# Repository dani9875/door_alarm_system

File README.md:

# Door alarm system
This project is a DIY smart door alarm system designed to enhance property security by providing real-time monitoring and notifications. The system detects whether a door has been opened or closed and instantly reacts to these events.

When a change is detected, the system transmits the event data through the local network to cloud services. The cloud then relays the information to a mobile application, alerting the property owner via a notification. This ensures the owner is promptly informed whenever someone enters or leaves the property.

*In case you are interested in making your own instance, please find the HW manufacturing files under the release tab.*

# How to build, flash and monitor the output the firmware
0. Check out the repository

1. Navigate to the `door_alarm_fw` directory:  
   ```bash
   cd door_alarm_fw
   ```

2. (Once) Build the Docker image by executing the following script if you have not done yet:  
   ```bash
   ./docker_build.sh
   ```

3. After the Docker image is successfully built, start the container using:  
   ```bash
   ./docker_start.sh
   ```

4. Configure the followings in *main.c* manually before build:

   ```c
   #define EXAMPLE_ESP_WIFI_SSID      "AP"
   #define EXAMPLE_ESP_WIFI_PASS      "password"

   #define EXAMPLE_STATIC_IP_ADDR        "192.168.0.100"
   #define EXAMPLE_STATIC_GW_ADDR        "192.168.0.1"
   #define EXAMPLE_STATIC_NETMASK_ADDR   "255.255.255.0"

   #define HOST "us-east-1-1.aws.cloud2.influxdata.com"
   #define PATH "/api/v2/write?orgID=[org_id]&bucket=[bucket_name]&precision=ns"
   #define TOKEN "Token [INFLUX_DB TOKEN]"
   ```

5. Inside the container, build the firmware by running:  
   ```bash
   ./build_firmware.sh
   ```

6. To program the firmware onto the device, use:  
   ```bash
   ./burn_firmware.sh
   ```

7. If you wish to observe the firmware's output, execute the monitoring script:  
   ```bash
   ./monitor_firmware.sh
   ```

## Release notes

### Version: v3.0
Changelog:
- Voltage divider resistor change
- Component library update

### Version: v2.0
Changelog:
- Component library organised
- Fuse introduced
- IP4283CZ10-TBR,115 ESD diodes

### Version: v1.0
Changelog:
- USB capability (does not work)
- USB active LED (erroneously glows even when operating from battery)
- Debug programming header
- Reed switch gate 
- Debug LED
- Voltage sense

# Technical solutions
The heart of the device is the reed sensor, which operates in normally open mode (the circuit remains open when the magnet and the reed sensor are aligned). This design choice minimizes power consumption, as no current is drawn when the door is closed. The system remains in deep sleep mode most of the time and can only be interrupted by an interaction, such as opening or closing the door. When the system wakes up, it checks the battery charge level and the door status, then initializes the WiFi connection to transmit this data to the cloud. 

A time-series data platform, [Influx](https://cloud2.influxdata.com/signup), is used to collect the data, and the data is forwarded to [Grafana](https://grafana.com/) for visualization. You can find the `grafana_door_alarm_system.json` file in the docs, which you can import to create a dashboard for monitoring the door status and battery level. Make sure to set the source ID (UID) to ensure proper functionality. 

If you would like to receive notifications about state changes, I recommend visiting [IFTTT](https://ifttt.com/explore). You can trigger events and subscribe to them. The ideal solution is to create a webhook that can be triggered from the ESP32 when it wakes up. However, this is a PRO feature. If you want to stay within the free tier, you can create a Google Sheet, set it as a trigger, and add a row (GDrive API is enabled). When a row is added, the subscriber can receive a WhatsApp message (note that with the free plan, the message may be delayed up to 1 hour).

### V2
After the component placement, I realized that the voltage measurement enable pin pad came off, so I rewired it to the LED enable pin. As a result, every time I measure the battery level, the LED briefly lights up. I also didn't have a fuse in my inventory, so I bypassed it with a direct connection. Since USB communication was functioning properly, I decided not to add the H1 straight header pins.

**How to check if the USB interface is working properly:**

Run ```lsusb``` and look for a device called ```Espressif USB JTAG/serial debug unit``` 

```bash
root@c7cc3ff0b21c:/project# lsusb
Bus 004 Device 001: ID 1d6b:0003  
Bus 003 Device 003: ID 046d:c52b Logitech USB Receiver
Bus 003 Device 002: ID 13d3:54b1 Azurewave Integrated Camera
Bus 003 Device 021: ID 303a:1001 Espressif USB JTAG/serial debug unit
Bus 003 Device 004: ID 0bda:c123 Realtek Bluetooth Radio
Bus 003 Device 001: ID 1d6b:0002  
Bus 002 Device 001: ID 1d6b:0003  
Bus 001 Device 001: ID 1d6b:0002 
```

**A short code snippet (main.c, app_main()) that allows you to check if the general LED blinks:**
```c
const uint8_t led_en = GPIO_NUM_14;

void app_main(void)
{
    gpio_reset_pin(led_en);
    gpio_set_direction(led_en, GPIO_MODE_OUTPUT);

    while(1)
    {
        gpio_set_level(led_en, 1);
        vTaskDelay(pdMS_TO_TICKS(1000));
        gpio_set_level(led_en, 0);
        vTaskDelay(pdMS_TO_TICKS(1000));
    }   

    return;
}
```
In a short test, I approached the reed sensor with the magnet, which triggered a wake-up event (the LED lights up). While I held the magnet in place, nothing further happened, and the device went back to sleep. As soon as I removed the magnet, the LED flashed again, indicating that the system had woken up, similar to how it would behave if the door were opened. </br>

Although I did not have a proper casing the setup was mounted above the entrance to collect data and analyze power consumption. Data was being monitored in Grafana. 

</br>

### V1
The first version was revised because the USB interface did not work at all, and it wasn’t even impedance-controlled. As a result, it had to be programmed via the UART interface using a USB-to-TTL adapter.

## Consumption calculations
Power usage estimates assume the application wakes up 6 times a day (3 times for door opening and 3 times for door closing), and the system is powered by 4 AA batteries with average capacity.

| **Component**              | **Current (µA)** | **Time (s)** | **Energy Contribution (µA·s)**   | **Comment**                                                                                          |
|----------------------------|------------------|--------------|-----------------------------------|------------------------------------------------------------------------------------------------------|
| AP2114HA-3.3TRG1           | 60              | 86400        | 60*86400 = 5184000  | LDO operates at all times.                                                                          |
| ESP32 awake doing its job  | 300000          | 60           | 300000*60 = 18000000| Wake-up duration is approximately 10 seconds.                                                      |
| Battery measurement        | 240             | 60           | 240*60 = 14400   | V_SENSE divider: ~ (6 V / 25000 Ω) = 240 µA, active only during wake-up periods.                    |
| Reed switch closed (door open)    | 330             | 45           | 330*45 = 14850      | The door is left open for a maximum of 15 seconds, and this state occurs during half of all activities. |
| ESP32 deep sleep mode      | 8               | 86340        | 8*86340 = 690720    | ESP32 consumes minimal power during deep sleep.                                                     |

#### Total Energy Contribution (µA·s):
$$
5184000 + 18000000 + 14400 + 14850 + 690720 = 23903970 \ \text{µAs}
$$

#### Average Current per day (µA):
$$
\text{Average Current} = \frac{23903970}{86400} \approx 276 \ \text{µA}
$$

**Assumptions:**
**4 AA batteries** in series: Each AA battery provides **1.5V**, and the combined voltage will be **6V**. **Capacity of AA batteries**: We'll assume **2000 mAh** for typical alkaline AA batteries. **Average current consumption**: **276 µA** (0.276 mA).
</br>

#### Battery life in hours can be calculated by dividing the total battery capacity by the current draw:

$$
\text{Battery Life (hours)} = \frac{\text{Battery Capacity (mAh)}}{\text{Current Consumption (mA)}}
$$

#### For **2000 mAh** batteries and **0.276 mA** current:

$$
\text{Battery Life (hours)} = \frac{2000}{0.276} \approx 7246 \, \text{hours}
$$

#### Convert this to days:

$$
\text{Battery Life (days)} = \frac{7246}{24} \approx 302 \, \text{days}
$$

**Calculation here is not final since batteries are not drained to 0 V. Will be added after some testing. LDO shall be fed at least from 4V.** 

## Limitations/what could be improved
- HW routing is not ideal
- Local wifi credentials and static IP as well as INFLUX_DB credentials must be compiled into the project and must be set from source code
- Consumptions increase when the door is open (around 400-500 uA)
- HW and FW project is tightly-coupled making versioning obscure
- Voltage divider resistors are mixed up
- Creation of a elegant enclosure is lacked
- Some FW clean-up

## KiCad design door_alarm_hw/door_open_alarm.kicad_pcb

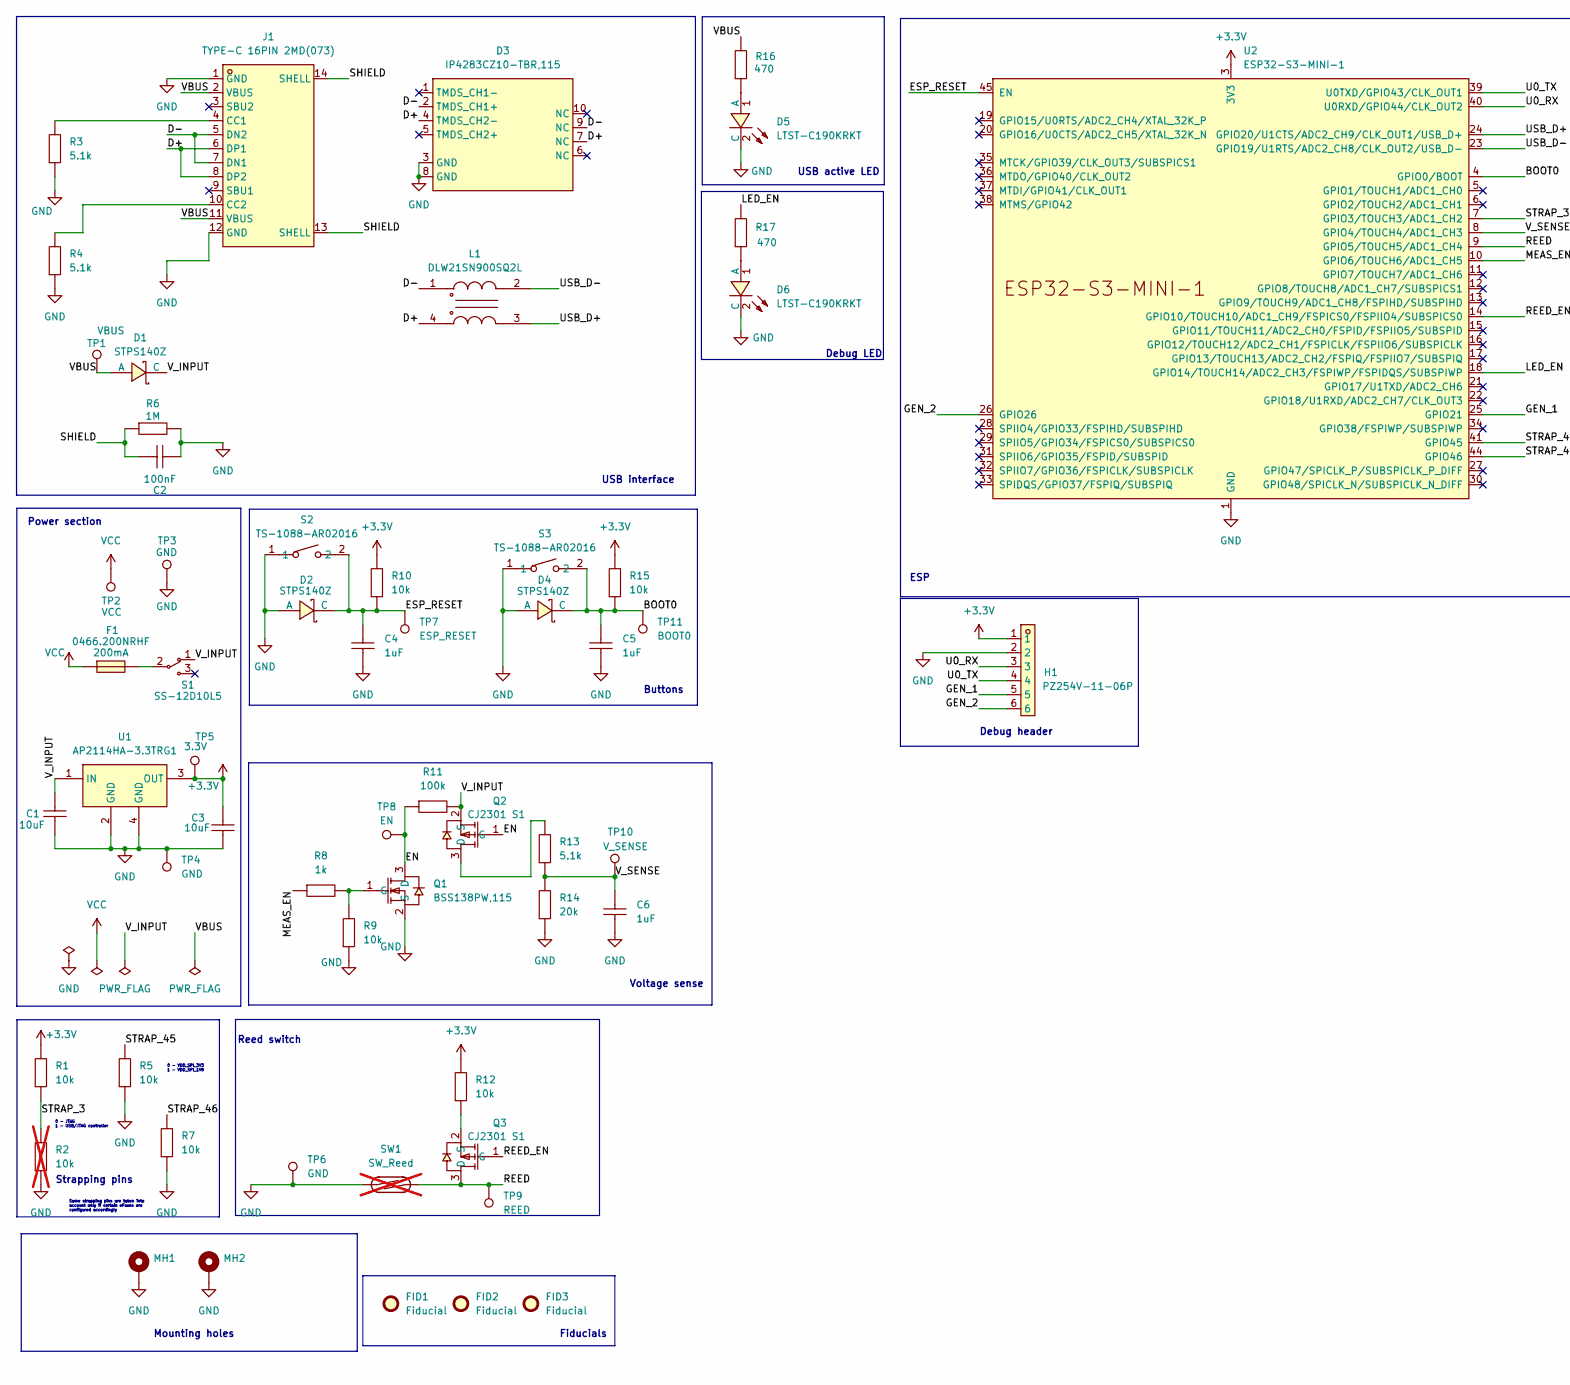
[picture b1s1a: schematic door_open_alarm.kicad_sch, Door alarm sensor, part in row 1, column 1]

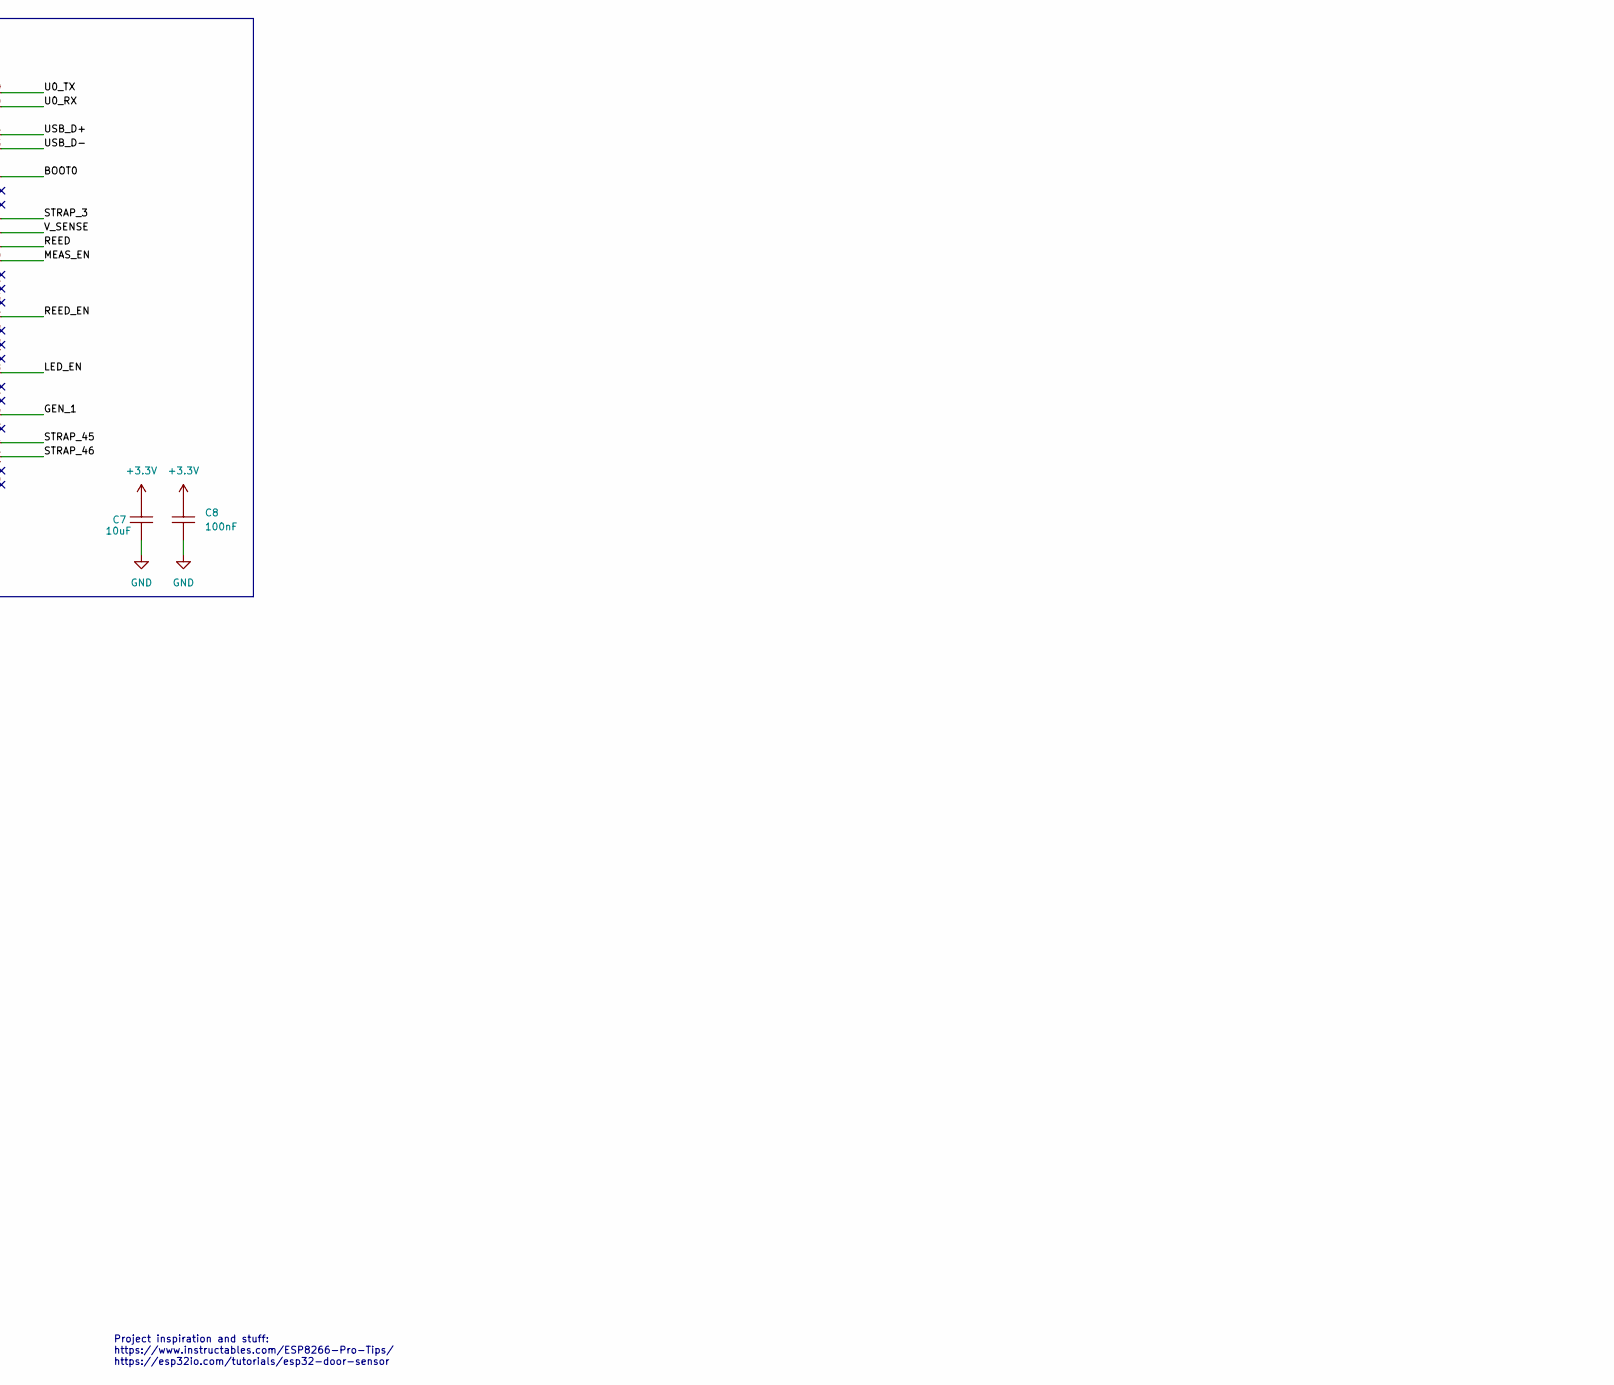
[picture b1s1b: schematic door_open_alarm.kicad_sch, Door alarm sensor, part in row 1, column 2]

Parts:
C1, C3, C7: CL21A106KOQNNNE; [CAP_SMD_0805_2012Metric]; LCSC Part C1713
C2, C8: CC0805KRX7R9BB104; [CAP_SMD_0805_2012Metric]; LCSC Part C49678
C4, C5, C6: C0805C105M4VACTU; [CAP_SMD_0805_2012Metric]; LCSC Part C2171722
D1, D2, D4: STPS140Z; [SCHOTTKY_DIODE_40V]STMicroelectronics STPS140Z; LCSC Part C155662
D3: IP4283CZ10-TBR,115; [ESD_PROT]Nexperia IP4283CZ10-TBR,115; LCSC Part C551514
D5, D6: LTST-C190KRKT; [LED]Lite-On LTST-C190KRKT; LCSC Part C94869
F1: 0466.200NRHF; [FUSE_SMD_1206]; LCSC Part C206985
FID1, FID2, FID3: Fiducial; Fiducial_0.5mm_Mask1mm
H1: PZ254V-11-06P; [6P_HEADER_STR]XFCN PZ254V-11-06P; LCSC Part C492405
J1: TYPE-C 16PIN 2MD(073); [USB_C_16P_RA_FEMALE]SHOU HAN TYPE-C 16PIN 2MD(073); LCSC Part C2765186
L1: DLW21SN900SQ2L; [COMMON_MODE_FILTER]Murata Electronics DLW21SN900SQ2L; LCSC Part C97856
MH1, MH2: [MOUNTING_HOLE]MountingHole_2.2mm_M2_DIN965_Pad
Q1: BSS138PW,115; [NMOS]Nexperia BSS138PW,115; LCSC Part C193366
Q2, Q3: CJ2301 S1; [PMOS]Jiangsu Changjing Electronics Technology Co., Ltd. CJ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; LCSC Part C8547
R1, R5, R7, R9, R10, R12, R15: 0805W8F1002T5E; [RES_SMD_0805_2012Metric]; LCSC Part C17414
R2: 0805W8F1002T5E; [RES_SMD_0805_2012Metric]; LCSC Part C17414; not fitted
R3, R4, R13: 0805W8F5101T5E; [RES_SMD_0805_2012Metric]; LCSC Part C27834
R6: 0805W8F1004T5E; [RES_SMD_0805_2012Metric]; LCSC Part C17514
R8: 0805W8F1001T5E; [RES_SMD_0805_2012Metric]; LCSC Part C17513
R11: 0805W8F1003T5E; [RES_SMD_0805_2012Metric]; LCSC Part C149504
R14: 0805W8J0203T5E; [RES_SMD_0805_2012Metric]; LCSC Part C25624
R16, R17: 0805W8F4700T5E; [RES_SMD_0805_2012Metric]; LCSC Part C17710
S1: SS-12D10L5; [SLIDE_SWITCH]XKB Connection SS-12D10L5; LCSC Part C319012
S2, S3: TS-1088-AR02016; [TACTILE_SWITCH]XUNPU TS-1088-AR02016; LCSC Part C720477
SW1: SW_Reed; not fitted
TP1: VBUS; [TEST_POINT]TestPoint_Pad_D1.0mm
TP2: VCC; [TEST_POINT]TestPoint_Pad_2.0x2.0mm
TP3: GND; [TEST_POINT]TestPoint_Pad_2.0x2.0mm
TP4, TP6: GND; [TEST_POINT]TestPoint_Pad_D1.0mm
TP5: 3.3V; [TEST_POINT]TestPoint_Pad_D1.0mm
TP7: ESP_RESET; [TEST_POINT]TestPoint_Pad_D1.0mm
TP8: EN; [TEST_POINT]TestPoint_Pad_D1.0mm
TP9: REED; [TEST_POINT]TestPoint_Pad_D1.0mm
TP10: V_SENSE; [TEST_POINT]TestPoint_Pad_D1.0mm
TP11: BOOT0; [TEST_POINT]TestPoint_Pad_D1.0mm
U1: AP2114HA-3.3TRG1; [LDO]Diodes Incorporated AP2114HA-3.3TRG1; LCSC Part C460314
U2: ESP32-S3-MINI-1; [MCU]Espressif Systems ESP32-S3-MINI-1-N8; LCSC Part C2913206

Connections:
+3.3V: C3.1, C7.1, C8.2, H1.1, R1.2, R10.2, R12.2, R15.2, TP5.1, U1.3 (OUT), U2.3 (3V3)
/BOOT0: C5.2, D4.1 (C), R15.1, S3.2, TP11.1, U2.4 (GPIO0/BOOT)
/D+: D3.4 (TMDS_CH2-), D3.7 (NC), J1.6 (DP1), J1.8 (DP2), L1.4
/D-: D3.2 (TMDS_CH1+), D3.9 (NC), J1.5 (DN2), J1.7 (DN1), L1.1
/EN: Q1.3 (D), Q2.1 (G), R11.1, TP8.1
/ESP_RESET: C4.2, D2.1 (C), R10.1, S2.2, TP7.1, U2.45 (EN)
/GEN_1: H1.5, U2.25 (GPIO21)
/GEN_2: H1.6, U2.26 (GPIO26)
/LED_EN: R17.2, U2.18 (GPIO14/TOUCH14/ADC2_CH3/FSPIWP/FSPIDQS/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)
/MEAS_EN: R8.1, U2.10 (GPIO6/TOUCH6/ADC1_CH5)
/REED: Q3.3 (D), SW1.2, TP9.1, U2.9 (GPIO5/TOUCH5/ADC1_CH4)
/REED_EN: Q3.1 (G), U2.14 (GPIO10/TOUCH10/ADC1_CH9/FSPICS0/FSPIIO4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)
/SHIELD: C2.1, J1.13 (SHELL), J1.14 (SHELL), R6.1
/STRAP_3: R1.1, R2.2, U2.7 (GPIO3/TOUCH3/ADC1_CH2)
/STRAP_45: R5.2, U2.41 (GPIO45)
/STRAP_46: R7.2, U2.44 (GPIO46)
/U0_RX: H1.3, U2.40 (U0RXD/GPIO44/CLK_OUT2)
/U0_TX: H1.4, U2.39 (U0TXD/GPIO43/CLK_OUT1)
/USB_D+: L1.3, U2.24 (GPIO20/U1CTS/ADC2_CH9/CLK_OUT1/USB_D+)
/USB_D-: L1.2, U2.23 (GPIO19/U1RTS/ADC2_CH8/CLK_OUT2/USB_D-)
/VBUS: D1.2 (A), J1.2 (VBUS), J1.11 (VBUS), R16.2, TP1.1
/V_INPUT: C1.1, D1.1 (C), Q2.2 (S), R11.2, S1.1, U1.1 (IN)
/V_SENSE: C6.2, R13.1, R14.2, TP10.1, U2.8 (GPIO4/TOUCH4/ADC1_CH3)
GND: C1.2, C2.2, C3.2, C4.1, C5.1, C6.1, C7.2, C8.1, D2.2 (A), D3.3 (GND), D3.8 (GND), D4.2 (A), D5.2 (C), D6.2 (C), H1.2, J1.1 (GND), J1.12 (GND), MH1.1, MH2.1, Q1.2 (S), R2.1, R3.1, R4.1, R5.1, R6.2, R7.1, R9.1, R14.1, S2.1, S3.1, SW1.1, TP3.1, TP4.1, TP6.1, U1.2 (GND), U1.4 (GND), U2.1 (GND), U2.2 (GND), U2.42 (GND), U2.43 (GND), U2.46 (GND), U2.47 (GND), U2.48 (GND), U2.49 (GND), U2.50 (GND), U2.51 (GND), U2.52 (GND), U2.53 (GND), U2.54 (GND), U2.55 (GND), U2.56 (GND), U2.57 (GND), U2.58 (GND), U2.59 (GND), U2.60 (GND), U2.61 (GND), U2.62 (GND), U2.63 (GND), U2.64 (GND), U2.65 (GND)
unnamed: D5.1 (A), R16.1
unnamed: D6.1 (A), R17.1
unnamed: F1.2, S1.2
unnamed: J1.4 (CC1), R3.2
unnamed: J1.10 (CC2), R4.2
unnamed: Q1.1 (G), R8.2, R9.2
unnamed: Q2.3 (D), R13.2
unnamed: Q3.2 (S), R12.1
VCC: F1.1, TP2.1

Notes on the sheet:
Debug header
USB interface
Mounting holes
Fiducials
USB active LED
4-6 GPIO 0.1 inches header-e -> VCC,GND stb
ESP
Buttons
0 - JTAG 1 - USB/JTAG controller
Project inspiration and stuff: https://www.instructables.com/ESP8266-Pro-Tips/ https://esp32io.com/tutorials/esp32-door-sensor
Debug LED
Voltage sense
Strapping pins
Some strapping pins are taken into account only if certain eFuses are configured accordingly
Power section
0 - VDD_SPI_3V3 1 - VDD_SPI_1V8
Reed switch

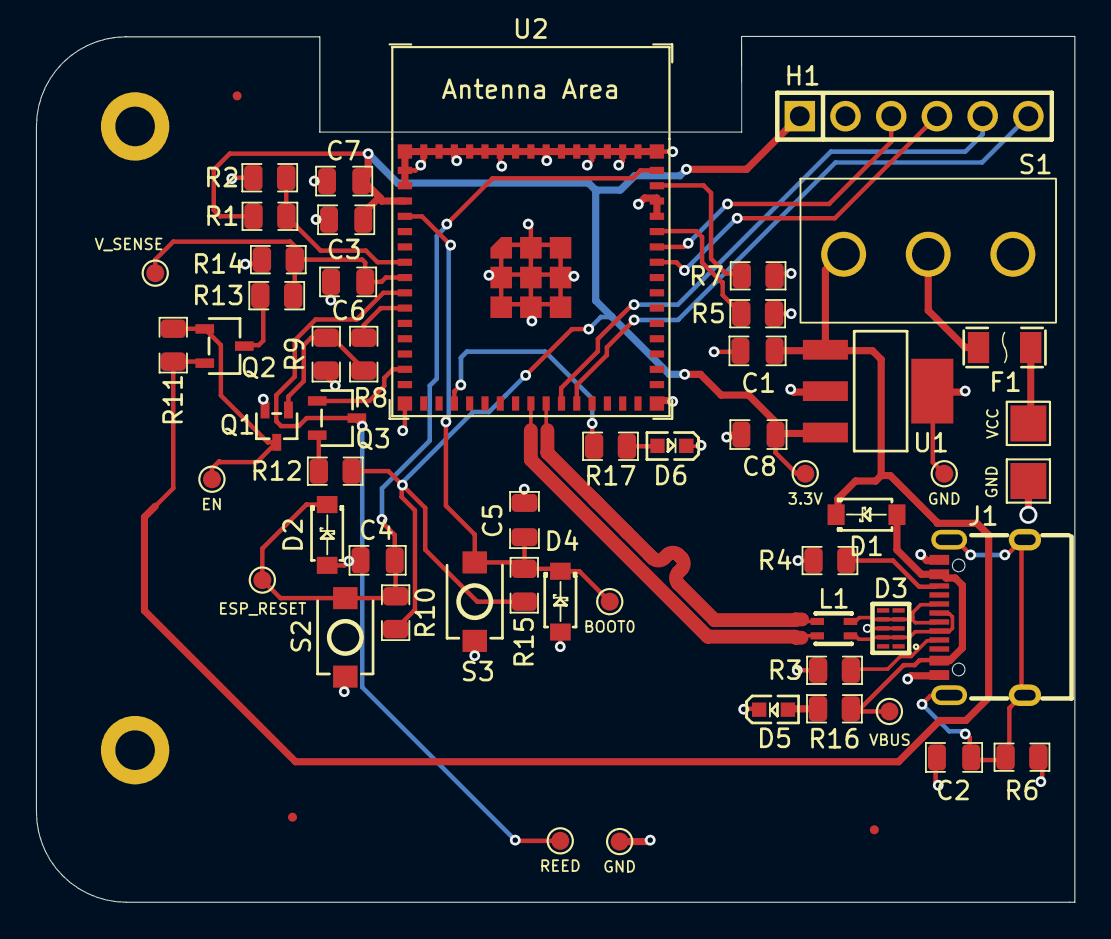
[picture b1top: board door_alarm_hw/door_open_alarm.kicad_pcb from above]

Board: 2 copper layers, 57.7 x 48.1 mm, 59 parts (0 on the bottom side), 33 nets.

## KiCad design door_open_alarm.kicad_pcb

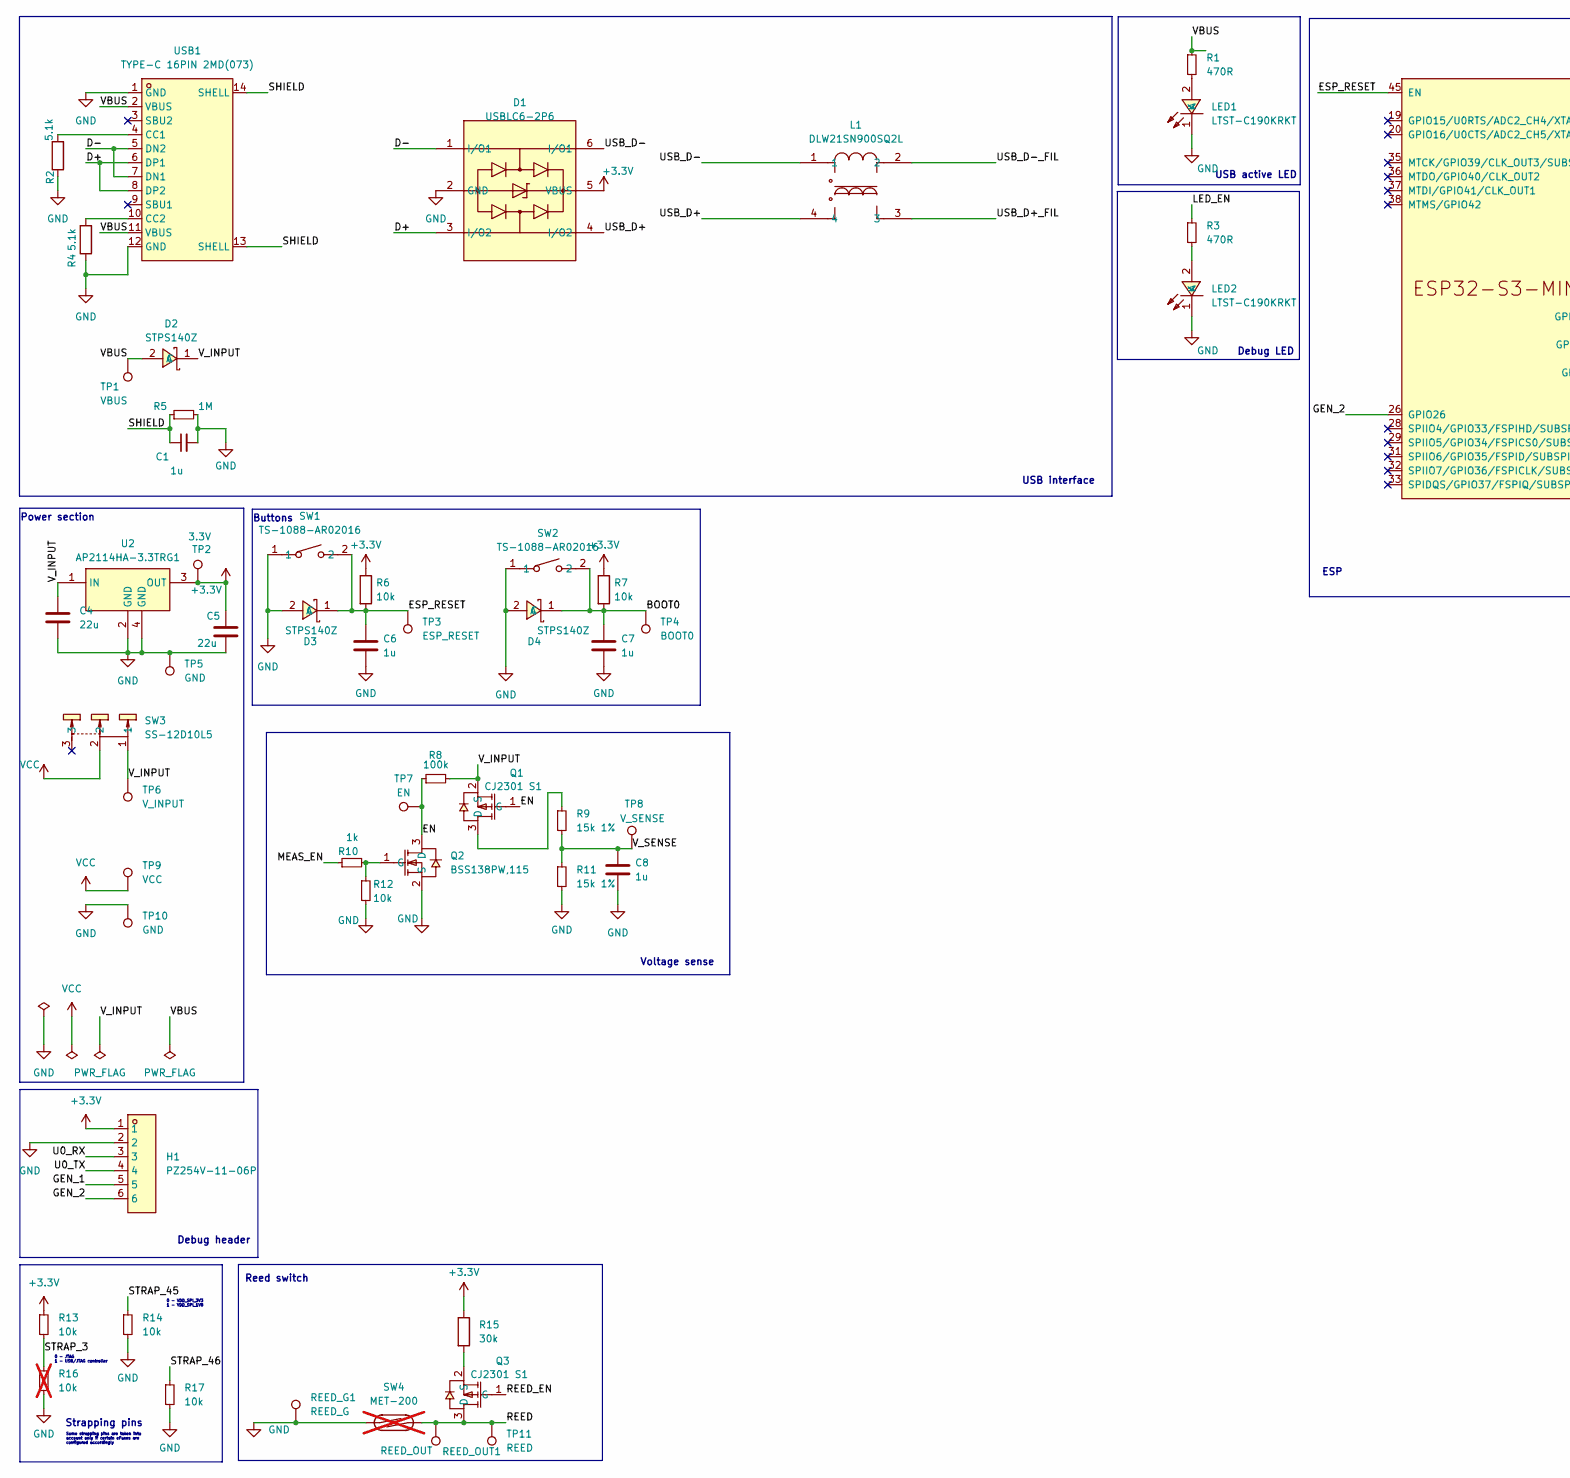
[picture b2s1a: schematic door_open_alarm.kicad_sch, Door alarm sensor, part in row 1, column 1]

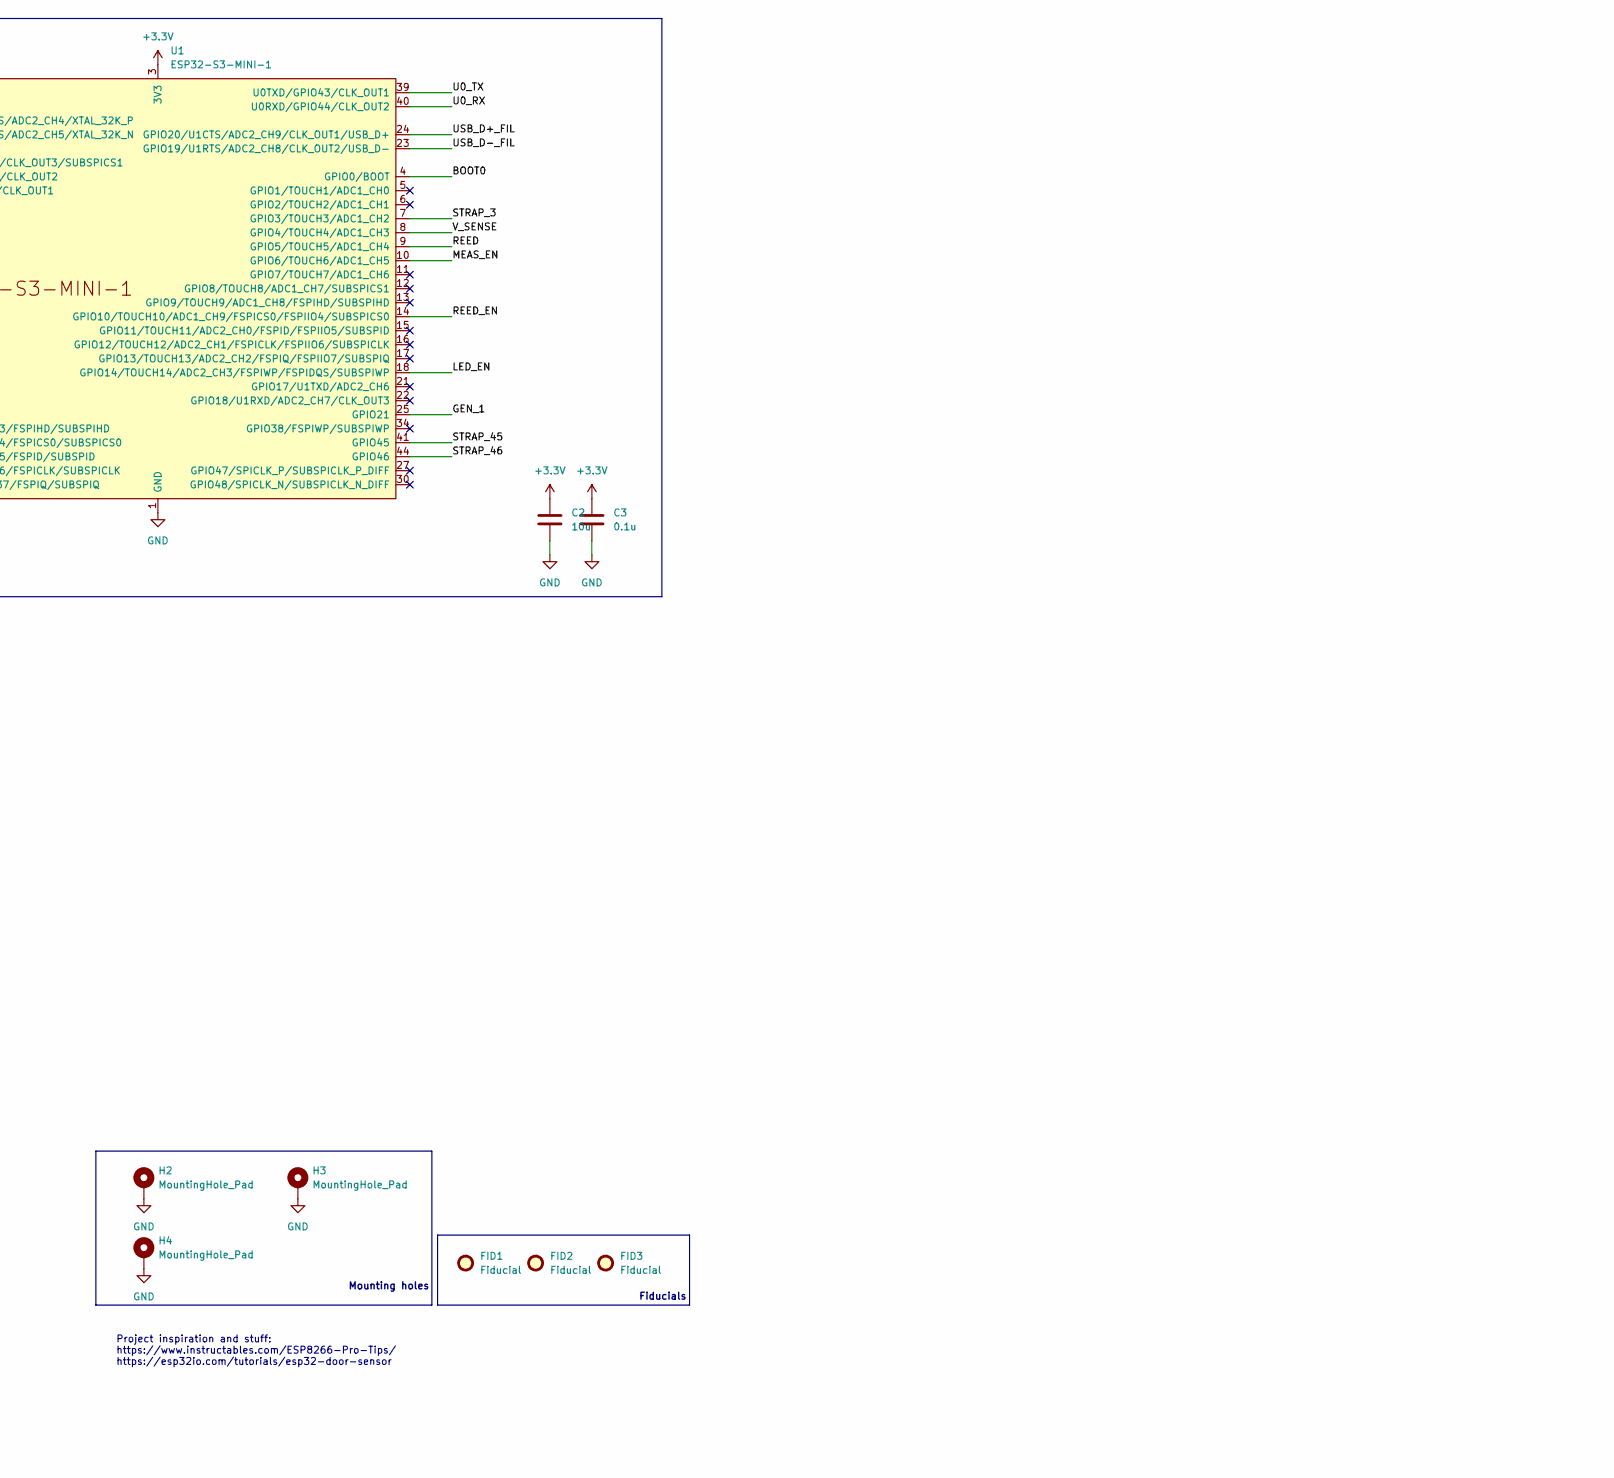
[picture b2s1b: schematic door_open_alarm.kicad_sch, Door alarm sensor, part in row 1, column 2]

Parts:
C1, C6, C7, C8: 1u; C_0805_2012Metric
C2: 10u; C_0805_2012Metric
C3: 0.1u; C_0805_2012Metric
C4, C5: 22u; C_0805_2012Metric
D1: USBLC6-2P6; SOT-666-6_L1.6-W1.2-P0.50-LS1.6-BR; LCSC Part C15999
D2, D3, D4: STPS140Z; SOD-123_L2.8-W1.8-LS3.7-RD; LCSC Part C155662
FID1, FID2, FID3: Fiducial; Fiducial_0.5mm_Mask1mm
H1: PZ254V-11-06P; [6P_HEADER_STR]XFCN PZ254V-11-06P; LCSC Part C492405
H2, H3, H4: MountingHole_Pad; MountingHole_2.2mm_M2_DIN965_Pad
L1: DLW21SN900SQ2L; FILTER-SMD_4P-L2.0-W1.2-BL_DLW21H; LCSC Part C97856
LED1, LED2: LTST-C190KRKT; [LED]Lite-On LTST-C190KRKT; LCSC Part C94869
Q1, Q3: CJ2301 S1; [PMOS]Jiangsu Changjing Electronics Technology Co., Ltd. CJ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; LCSC Part C8547
Q2: BSS138PW,115; [NMOS]Nexperia BSS138PW,115; LCSC Part C193366
R1, R3: 470R; R_0805_2012Metric
R2, R4: 5.1k; R_0805_2012Metric
R5: 1M; R_0805_2012Metric
R6, R7, R12, R13, R14, R17: 10k; R_0805_2012Metric
R8: 100k; R_0805_2012Metric
R9, R11: 15k 1%; R_0805_2012Metric
R10: 1k; R_0805_2012Metric
R15: 30k; R_0805_2012Metric
R16: 10k; R_0805_2012Metric; not fitted
REED_G1: REED_G; TestPoint_Pad_2.0x2.0mm
REED_OUT1: REED_OUT; TestPoint_Pad_2.0x2.0mm
SW1, SW2: TS-1088-AR02016; [TACTILE_SWITCH]XUNPU TS-1088-AR02016; LCSC Part C720477
SW3: SS-12D10L5; [SLIDE_SWITCH]XKB Connection SS-12D10L5; LCSC Part C319012
SW4: MET-200; not fitted
TP1: VBUS; TestPoint_Pad_D1.0mm
TP2: 3.3V; TestPoint_Pad_D1.0mm
TP3: ESP_RESET; TestPoint_Pad_D1.0mm
TP4: BOOT0; TestPoint_Pad_D1.0mm
TP5: GND; TestPoint_Pad_D1.0mm
TP6: V_INPUT; TestPoint_Pad_D1.0mm
TP7: EN; TestPoint_Pad_D1.0mm
TP8: V_SENSE; TestPoint_Pad_D1.0mm
TP9: VCC; TestPoint_Pad_2.0x2.0mm
TP10: GND; TestPoint_Pad_2.0x2.0mm
TP11: REED; TestPoint_Pad_D1.0mm
U1: ESP32-S3-MINI-1
U2: AP2114HA-3.3TRG1; [LDO]Diodes Incorporated AP2114HA-3.3TRG1; LCSC Part C460314
USB1: TYPE-C 16PIN 2MD(073); USB-C-SMD_TYPE-C-6PIN-2MD-073; LCSC Part C2765186

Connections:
+3.3V: C2.1, C3.1, C5.1, D1.5 (VBUS), H1.1, R6.1, R7.1, R13.1, R15.1, TP2.1, U1.3 (3V3), U2.3 (OUT)
/BOOT0: C7.1, D4.1 (C), R7.2, SW2.2, TP4.1, U1.4 (GPIO0/BOOT); also elsewhere on the board
/D+: D1.3 (I/O2), USB1.6 (DP1), USB1.8 (DP2)
/D-: D1.1 (I/O1), USB1.5 (DN2), USB1.7 (DN1)
/EN: Q1.1 (G), Q2.3 (D), R8.1, TP7.1
/ESP_RESET: C6.1, D3.1 (C), R6.2, SW1.2, TP3.1, U1.45 (EN); also elsewhere on the board
/GEN_1: H1.5, U1.25 (GPIO21)
/GEN_2: H1.6, U1.26 (GPIO26)
/LED_EN: R3.1, U1.18 (GPIO14/TOUCH14/ADC2_CH3/FSPIWP/FSPIDQS/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)
/MEAS_EN: R10.1, U1.10 (GPIO6/TOUCH6/ADC1_CH5)
/REED: Q3.3 (D), REED_OUT1.1, SW4.2, TP11.1, U1.9 (GPIO5/TOUCH5/ADC1_CH4)
/REED_EN: Q3.1 (G), U1.14 (GPIO10/TOUCH10/ADC1_CH9/FSPICS0/FSPIIO4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)
/SHIELD: C1.1, R5.1, USB1.13 (SHELL), USB1.14 (SHELL)
/STRAP_3: R13.2, R16.1, U1.7 (GPIO3/TOUCH3/ADC1_CH2)
/STRAP_45: R14.1, U1.41 (GPIO45)
/STRAP_46: R17.1, U1.44 (GPIO46)
/U0_RX: H1.3, U1.40 (U0RXD/GPIO44/CLK_OUT2)
/U0_TX: H1.4, U1.39 (U0TXD/GPIO43/CLK_OUT1)
/USB_D+: D1.4 (I/O2), L1.4
/USB_D+_FIL: L1.3, U1.24 (GPIO20/U1CTS/ADC2_CH9/CLK_OUT1/USB_D+)
/USB_D-: D1.6 (I/O1), L1.1
/USB_D-_FIL: L1.2, U1.23 (GPIO19/U1RTS/ADC2_CH8/CLK_OUT2/USB_D-)
/VBUS: D2.2 (A), R1.1, TP1.1, USB1.2 (VBUS), USB1.11 (VBUS)
/V_INPUT: C4.1, D2.1 (C), Q1.2 (S), R8.2, SW3.1, TP6.1, U2.1 (IN)
/V_SENSE: C8.1, R9.2, R11.1, TP8.1, U1.8 (GPIO4/TOUCH4/ADC1_CH3)
GND: C1.2, C2.2, C3.2, C4.2, C5.2, C6.2, C7.2, C8.2, D1.2 (GND), D3.2 (A), D4.2 (A), H1.2, H2.1, H3.1, H4.1, LED1.1 (K), LED2.1 (K), Q2.2 (S), R2.1, R4.1, R5.2, R11.2, R12.2, R14.2, R16.2, R17.2, REED_G1.1, SW1.1, SW2.1, SW4.1, TP5.1, TP10.1, U1.1 (GND), U1.2 (GND), U1.42 (GND), U1.43 (GND), U1.46 (GND), U1.47 (GND), U1.48 (GND), U1.49 (GND), U1.50 (GND), U1.51 (GND), U1.52 (GND), U1.53 (GND), U1.54 (GND), U1.55 (GND), U1.56 (GND), U1.57 (GND), U1.58 (GND), U1.59 (GND), U1.60 (GND), U1.61 (GND), U1.62 (GND), U1.63 (GND), U1.64 (GND), U1.65 (GND), U2.2 (GND), U2.4 (GND), USB1.1 (GND), USB1.12 (GND); also elsewhere on the board
unnamed: LED1.2 (A), R1.2
unnamed: LED2.2 (A), R3.2
unnamed: Q1.3 (D), R9.1
unnamed: Q2.1 (G), R10.2, R12.1
unnamed: Q3.2 (S), R15.2
unnamed: R2.2, USB1.4 (CC1)
unnamed: R4.2, USB1.10 (CC2)
VCC: SW3.2, TP9.1; also elsewhere on the board

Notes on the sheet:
Debug header
USB interface
Mounting holes
Fiducials
USB active LED
4-6 GPIO 0.1 inches header-e -> VCC,GND stb
ESP
Buttons
0 - JTAG 1 - USB/JTAG controller
Project inspiration and stuff: https://www.instructables.com/ESP8266-Pro-Tips/ https://esp32io.com/tutorials/esp32-door-sensor
Debug LED
Voltage sense
Strapping pins
Some strapping pins are taken into account only if certain eFuses are configured accordingly
Power section
0 - VDD_SPI_3V3 1 - VDD_SPI_1V8
Reed switch

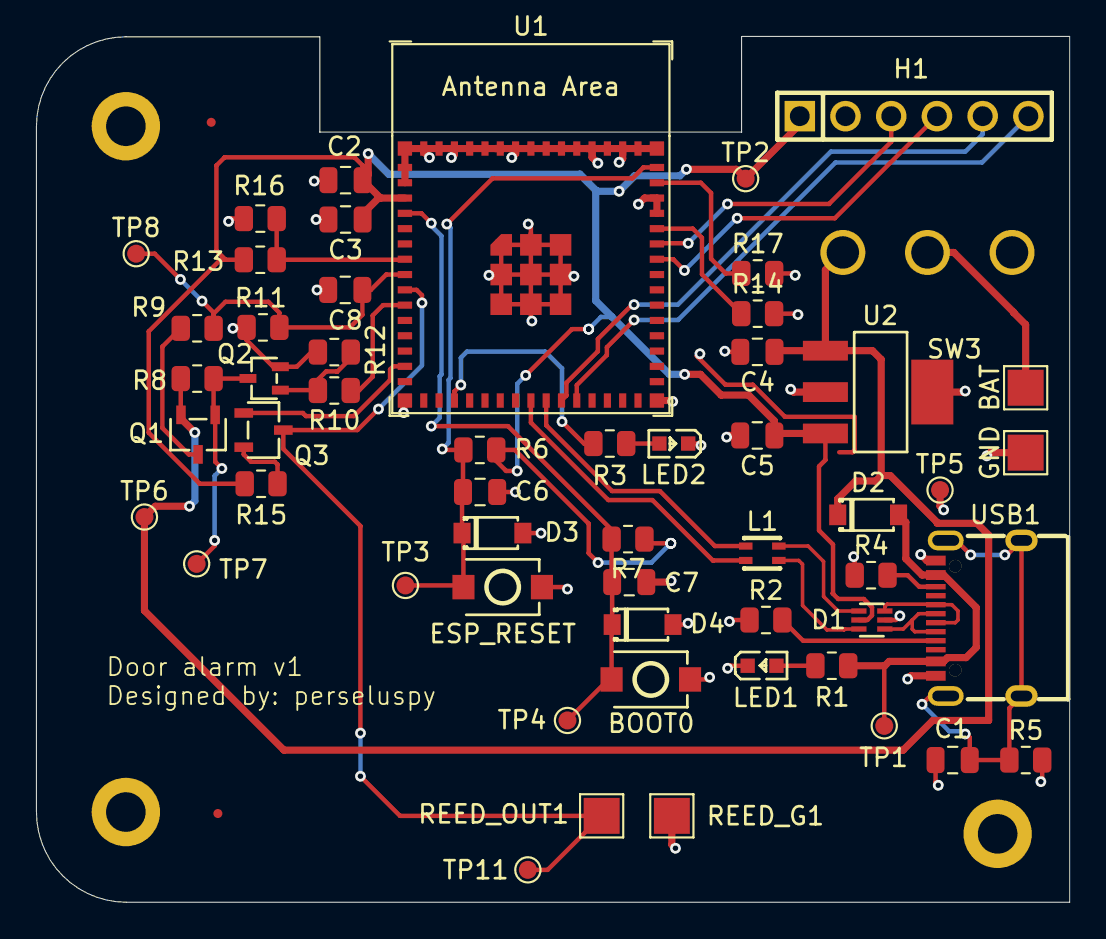
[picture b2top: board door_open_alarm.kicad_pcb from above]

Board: 2 copper layers, 57.4 x 48.1 mm, 60 parts (0 on the bottom side), 34 nets.

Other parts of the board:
BAT: VCC; TestPoint_Pad_2.0x2.0mm
BOOT0: TS-1088-AR02016; [TACTILE_SWITCH]XUNPU TS-1088-AR02016
ESP_RESET: TS-1088-AR02016; [TACTILE_SWITCH]XUNPU TS-1088-AR02016
GND: GND; TestPoint_Pad_2.0x2.0mm

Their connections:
/BOOT0: BOOT0.2; also elsewhere on the board
/ESP_RESET: ESP_RESET.2; also elsewhere on the board
GND: BOOT0.1, ESP_RESET.1, GND.1; also elsewhere on the board
VCC: BAT.1; also elsewhere on the board

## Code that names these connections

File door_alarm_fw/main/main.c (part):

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
adc_cali_handle_t                       cali_handle;
adc_oneshot_unit_handle_t               adc_handle;
const uint8_t reed_en = GPIO_NUM_10;
const uint8_t door_sensor = GPIO_NUM_5;
const uint8_t meas_en = GPIO_NUM_6;
const uint8_t led_en = GPIO_NUM_14;


float voltage;
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     }


    gpio_reset_pin(led_en);
    gpio_set_direction(led_en, GPIO_MODE_OUTPUT);
    gpio_set_level(led_en, 1);
    vTaskDelay(pdMS_TO_TICKS(200));

    adc_init(ADC_UNIT_1, ADC_CHANNEL_3, ADC_ATTEN_DB_11, ADC_BITWIDTH_DEFAULT);
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    adc_oneshot_read(adc_handle, ADC_CHANNEL_3, &adc_raw);
    adc_cali_raw_to_voltage(cali_handle, adc_raw, &vbus_V);

    gpio_set_level(led_en, 0);

    voltage = (25.1/5.1)*((float)vbus_V/1000);

    ESP_LOGI("MAIN", "Voltage level: %f", voltage);
    ESP_LOGI("MAIN", "Voltage level raw: %d", vbus_V);

    rtc_gpio_hold_dis(reed_en);
    rtc_gpio_init(reed_en);
    rtc_gpio_set_direction(reed_en, RTC_GPIO_MODE_OUTPUT_ONLY);
    rtc_gpio_set_level(reed_en, 0);

    vTaskDelay(pdMS_TO_TICKS(10));

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        esp_sleep_enable_ext0_wakeup(door_sensor, 1);

        rtc_gpio_pullup_en(door_sensor);
        rtc_gpio_set_level(reed_en, 0);
        rtc_gpio_hold_en(reed_en); 
        ESP_LOGI("MAIN", "Open door");

    }
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        esp_sleep_enable_ext0_wakeup(door_sensor, 0);

        rtc_gpio_pullup_en(door_sensor);
        rtc_gpio_set_level(reed_en, 0);
        rtc_gpio_hold_en(reed_en); 
        ESP_LOGI("MAIN", "Closed door");
    }
    prev_level = level;
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
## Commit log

2024-05-14 Removing manuf files
2024-05-14 Init fw files
2024-06-02 Adding gitignore
2024-06-04 Gathering HW files in one folder
2024-06-05 Posting event to IFTTT
2024-06-08 ++commit
2024-06-09 test workflow
2024-06-24 Some FW changes
2024-06-27 Bulk change after component lib change
2024-06-28 Updating components and design as well as yaml
2024-07-01 Overhaul
2024-07-01 change++
2024-07-03 First working status reporter code
2024-07-20 Overhauling...
2024-07-20 Release workflow
2024-07-20 Readme update
2024-07-20 Changing config file path
2024-07-20 Chaning path for zip
2024-07-20 Path change in release step
2024-07-20 perseluspy component library added
2024-12-06 How to build the firmware
2024-12-06 Changes due to library update (minor)
2024-12-06 Version change for checkout in release.yml
2024-12-06 Version at wrong line
2024-12-09 Refinement to bringup v2 and README changes
2024-12-10 Cleanup of main
2024-12-11 Cons. calculations
2024-12-11 Massive README update
2024-12-11 Commit++
2024-12-11 Readme change
2024-12-11 Commit ++
2024-12-11 Trying to fix README format error
2024-12-11 Resistor mix up fix, label fix
2024-12-11 Update to v5 component library
2024-12-11 README update with v3 notes
2024-12-11 Mounted setup docs appended
2024-12-11 README correction
2024-12-20 MinUnit added for target tests
2025-01-15 Test API hosting
2025-01-27 Update swagger
2025-01-28 AWS solution
2026-01-01 latest
